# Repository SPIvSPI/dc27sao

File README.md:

# dc27sao

	███████╗██████╗ ██╗██╗   ██╗███████╗██████╗ ██╗
	██╔════╝██╔══██╗██║██║   ██║██╔════╝██╔══██╗██║
	███████╗██████╔╝██║██║   ██║███████╗██████╔╝██║
	╚════██║██╔═══╝ ██║╚██╗ ██╔╝╚════██║██╔═══╝ ██║
	███████║██║     ██║ ╚████╔╝ ███████║██║     ██║
	╚══════╝╚═╝     ╚═╝  ╚═══╝  ╚══════╝╚═╝     ╚═╝

Blackhat spy &amp; Whitehat spy SAO from Def Con 27

The pencil sketch that started it all on June 14th:

Bling bling:

## WTF is all this crap

- `/firmware` - shitty code that runs the blinkenlites
- `/gui` - not-so-shitty gui animation code generator tool (with shittyness added in a rush at the end)
- `/hardware` - schematics and pcb stuff
- `/img` - some pix from the adventure

## Other crap

- The twitters https://twitter.com/SPIvSPI
- Hackaday page https://hackaday.io/project/166811-spivspi-sao-dc27-badge

## Guilty Parties

```
xres0nance - Hardware & firmware
steve/corelit - Over-excellent GUI animation tool
```

## Shoutz n Greetz

```
true, cprossu, aask, & WP crew - 8051 wisdom and moral support
jrwr - crazy drunk russians and a dope-ass hat
MCB - melted lead shoulder-to-shoulder, six pins at a time
woodencyborg - for diving in the deep end with us
pcbway - haulin' ass, gettin' paid
```

and thanks to all our other cheerleaders! couldn't have done it without ya.

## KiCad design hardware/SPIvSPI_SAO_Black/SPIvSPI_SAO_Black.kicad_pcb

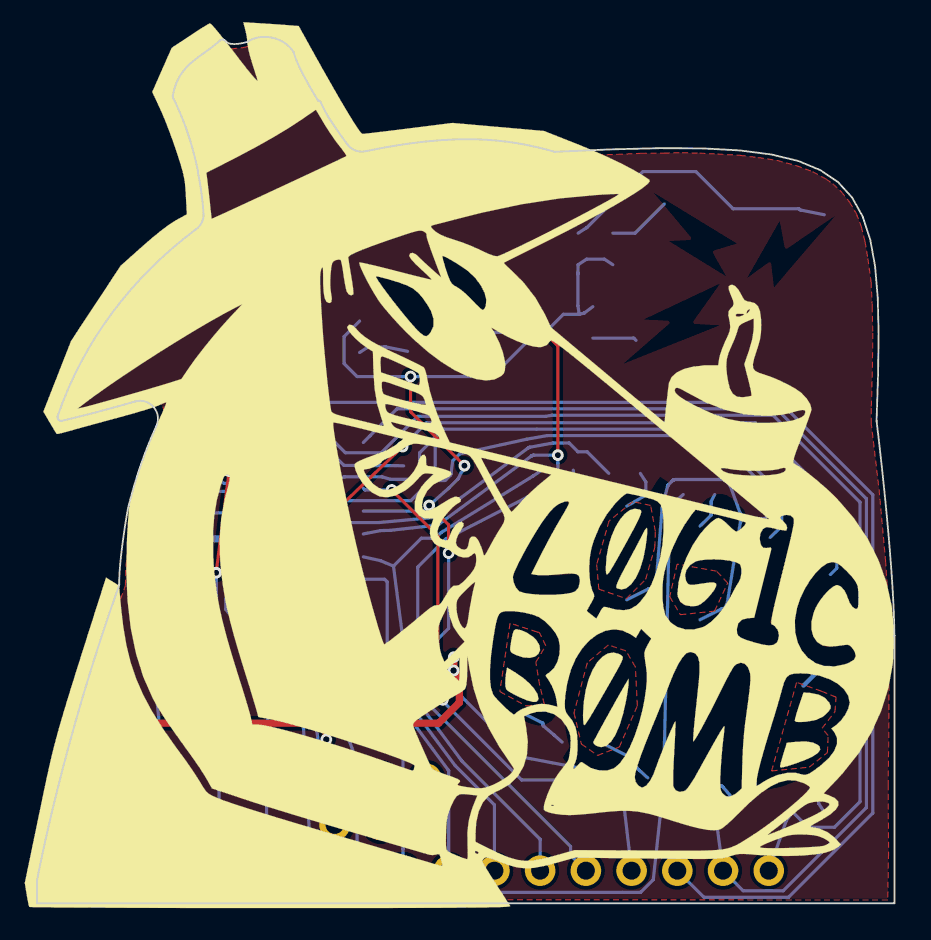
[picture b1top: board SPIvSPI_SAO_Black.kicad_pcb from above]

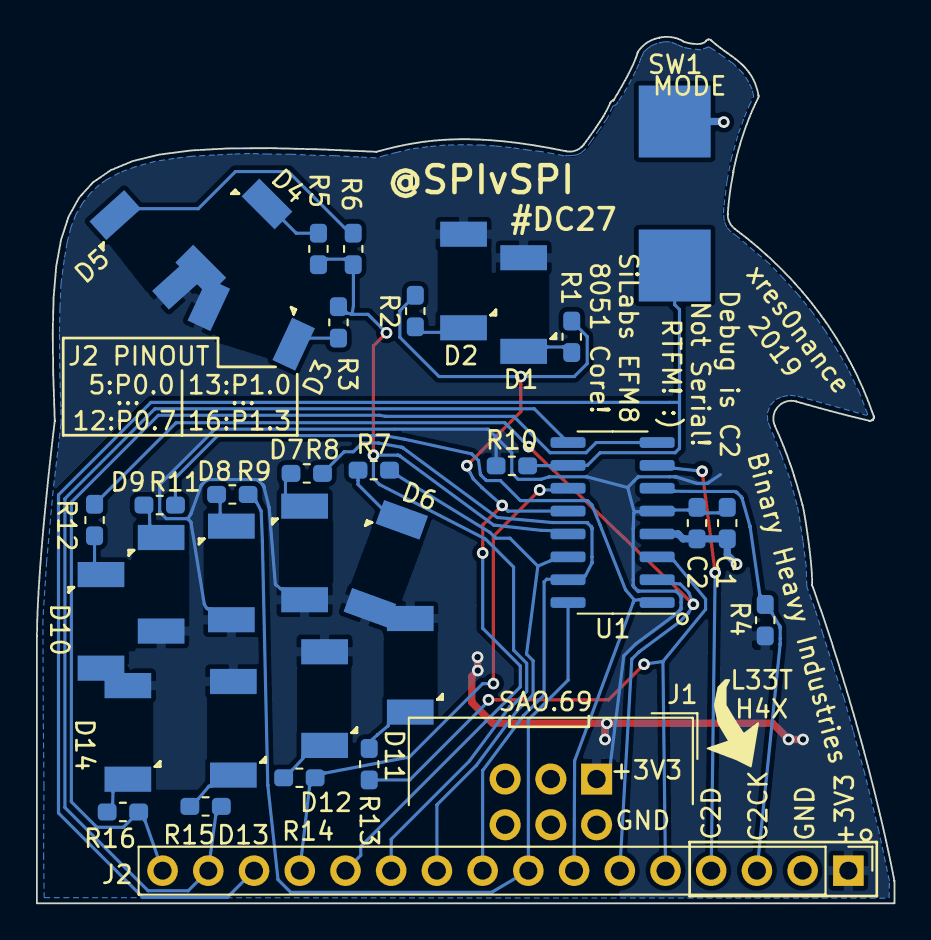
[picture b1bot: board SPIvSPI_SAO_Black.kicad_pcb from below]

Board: 2 copper layers, 47.6 x 48.1 mm, 36 parts (36 on the bottom side), 30 nets.

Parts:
C1: 0.1uF; C_0603_1608Metric_Pad1.05x0.95mm_HandSolder
C2: 10uF; C_0603_1608Metric_Pad1.05x0.95mm_HandSolder
D1, D2: RED; SunLED_3.2x2.8mm_PLCC2_bottom
D3, D4, D5: YEL; SunLED_3.2x2.8mm_PLCC2_bottom
D6, D7, D8, D9, D10, D11, D12, D13, D14: GRN; SunLED_3.2x2.8mm_PLCC2_bottom
J1: SAO.69; IDC-Header_2x03_P2.54mm_Vertical
J2: PROG/BREAKOUT; PinHeader_1x16_P2.54mm_Vertical
R1, R2, R7, R8, R9, R11, R12, R13, R14, R15, R16: 330; R_0603_1608Metric_Pad1.05x0.95mm_HandSolder
R3, R5, R6: 220; R_0603_1608Metric_Pad1.05x0.95mm_HandSolder
R4: 1K; R_0603_1608Metric_Pad1.05x0.95mm_HandSolder
R10: DNP; R_0603_1608Metric_Pad1.05x0.95mm_HandSolder
SW1: MODE; C&K_PTS636_SMD_Tact_6.0x3.5_BACK
U1: EFM8BB10F8G-A-SOIC16; SOIC-16_3.9x9.9mm_P1.27mm

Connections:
+3V3: C1.1, C2.1, D1.2, D2.2, D3.2, D4.2, D5.2, D6.2, D7.2, D8.2, D9.2, D10.2, D11.2, D12.2, D13.2, D14.2, J1.1, J2.1, R4.1, R10.1, U1.5
GND: C1.2, C2.2, J1.2, J2.2, SW1.2, U1.4
unnamed: D1.1, R1.1
unnamed: D2.1, R2.1
unnamed: D3.1, R3.1
unnamed: D4.1, R5.1
unnamed: D5.1, R6.1
unnamed: D6.1, R7.1
unnamed: D7.1, R8.1
unnamed: D8.1, R9.1
unnamed: D9.1, R11.1
unnamed: D10.1, R12.1
unnamed: D11.1, R13.1
unnamed: D12.1, R14.1
unnamed: D13.1, R15.1
unnamed: D14.1, R16.1
unnamed: J2.3, R4.2, U1.6
unnamed: J2.4, U1.7
unnamed: J2.5, R13.2, U1.3
unnamed: J2.6, R12.2, U1.2
unnamed: J2.7, R11.2, U1.1
unnamed: J2.8, R9.2, U1.16
unnamed: J2.9, R8.2, U1.15
unnamed: J2.10, R7.2, U1.14
unnamed: J2.11, R3.2, R5.2, R6.2, U1.13
unnamed: J2.12, R1.2, R2.2, U1.12
unnamed: J2.13, R14.2, U1.11
unnamed: J2.14, R10.2, SW1.1, U1.10
unnamed: J2.15, R15.2, U1.9
unnamed: J2.16, R16.2, U1.8

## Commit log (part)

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2019-07-13 soon
2019-07-13 readme
2019-08-15 stuff
2019-08-15 crap
2020-04-04 Bump acorn from 5.7.3 to 5.7.4 in /gui
    Bumps [acorn](https://github.com/acornjs/acorn) from 5.7.3 to 5.7.4.
    - [Release notes](https://github.com/acornjs/acorn/releases)
    - [Commits](https://github.com/acornjs/acorn/compare/5.7.3...5.7.4)
2020-06-07 Bump websocket-extensions from 0.1.3 to 0.1.4 in /gui
    Bumps [websocket-extensions](https://github.com/faye/websocket-extensions-node) from 0.1.3 to 0.1.4.
    - [Release notes](https://github.com/faye/websocket-extensions-node/releases)
    - [Changelog](https://github.com/faye/websocket-extensions-node/blob/master/CHANGELOG.md)
    - [Commits](https://github.com/faye/websocket-extensions-node/compare/0.1.3...0.1.4)
2020-07-18 Bump lodash from 4.17.15 to 4.17.19 in /gui
    Bumps [lodash](https://github.com/lodash/lodash) from 4.17.15 to 4.17.19.
    - [Release notes](https://github.com/lodash/lodash/releases)
    - [Commits](https://github.com/lodash/lodash/compare/4.17.15...4.17.19)
2020-07-31 Bump elliptic from 6.5.0 to 6.5.3 in /gui
    Bumps [elliptic](https://github.com/indutny/elliptic) from 6.5.0 to 6.5.3.
    - [Release notes](https://github.com/indutny/elliptic/releases)
    - [Commits](https://github.com/indutny/elliptic/compare/v6.5.0...v6.5.3)
2020-09-10 Bump http-proxy from 1.17.0 to 1.18.1 in /gui
    Bumps [http-proxy](https://github.com/http-party/node-http-proxy) from 1.17.0 to 1.18.1.
    - [Release notes](https://github.com/http-party/node-http-proxy/releases)
    - [Changelog](https://github.com/http-party/node-http-proxy/blob/master/CHANGELOG.md)
    - [Commits](https://github.com/http-party/node-http-proxy/compare/1.17.0...1.18.1)
2020-09-12 Bump node-fetch from 2.6.0 to 2.6.1 in /gui
    Bumps [node-fetch](https://github.com/bitinn/node-fetch) from 2.6.0 to 2.6.1.
    - [Release notes](https://github.com/bitinn/node-fetch/releases)
    - [Changelog](https://github.com/node-fetch/node-fetch/blob/master/docs/CHANGELOG.md)
    - [Commits](https://github.com/bitinn/node-fetch/compare/v2.6.0...v2.6.1)
2020-11-25 Bump highlight.js from 9.15.8 to 9.18.5 in /gui
    Bumps [highlight.js](https://github.com/highlightjs/highlight.js) from 9.15.8 to 9.18.5.
    - [Release notes](https://github.com/highlightjs/highlight.js/releases)
    - [Changelog](https://github.com/highlightjs/highlight.js/blob/9.18.5/CHANGES.md)
    - [Commits](https://github.com/highlightjs/highlight.js/compare/9.15.8...9.18.5)
2021-03-09 Bump elliptic from 6.5.0 to 6.5.4 in /gui
    Bumps [elliptic](https://github.com/indutny/elliptic) from 6.5.0 to 6.5.4.
    - [Release notes](https://github.com/indutny/elliptic/releases)
    - [Commits](https://github.com/indutny/elliptic/compare/v6.5.0...v6.5.4)
2021-03-11 Bump dot-prop from 4.2.0 to 4.2.1 in /gui
    Bumps [dot-prop](https://github.com/sindresorhus/dot-prop) from 4.2.0 to 4.2.1.
    - [Release notes](https://github.com/sindresorhus/dot-prop/releases)
    - [Commits](https://github.com/sindresorhus/dot-prop/compare/v4.2.0...v4.2.1)
2021-03-11 Bump yargs-parser from 5.0.0 to 5.0.1 in /gui
    Bumps [yargs-parser](https://github.com/yargs/yargs-parser) from 5.0.0 to 5.0.1.
    - [Release notes](https://github.com/yargs/yargs-parser/releases)
    - [Changelog](https://github.com/yargs/yargs-parser/blob/v5.0.1/CHANGELOG.md)
    - [Commits](https://github.com/yargs/yargs-parser/compare/v5.0.0...v5.0.1)
2021-05-08 Bump url-parse from 1.4.7 to 1.5.1 in /gui
    Bumps [url-parse](https://github.com/unshiftio/url-parse) from 1.4.7 to 1.5.1.
    - [Release notes](https://github.com/unshiftio/url-parse/releases)
    - [Commits](https://github.com/unshiftio/url-parse/compare/1.4.7...1.5.1)
2021-05-10 Bump lodash from 4.17.19 to 4.17.21 in /gui
    Bumps [lodash](https://github.com/lodash/lodash) from 4.17.19 to 4.17.21.
    - [Release notes](https://github.com/lodash/lodash/releases)
    - [Commits](https://github.com/lodash/lodash/compare/4.17.19...4.17.21)
2021-05-11 Bump hosted-git-info from 2.7.1 to 2.8.9 in /gui
    Bumps [hosted-git-info](https://github.com/npm/hosted-git-info) from 2.7.1 to 2.8.9.
    - [Release notes](https://github.com/npm/hosted-git-info/releases)
    - [Changelog](https://github.com/npm/hosted-git-info/blob/v2.8.9/CHANGELOG.md)
    - [Commits](https://github.com/npm/hosted-git-info/compare/v2.7.1...v2.8.9)
2021-05-25 Bump browserslist from 4.6.6 to 4.16.6 in /gui
    Bumps [browserslist](https://github.com/browserslist/browserslist) from 4.6.6 to 4.16.6.
    - [Release notes](https://github.com/browserslist/browserslist/releases)
    - [Changelog](https://github.com/browserslist/browserslist/blob/main/CHANGELOG.md)
    - [Commits](https://github.com/browserslist/browserslist/compare/4.6.6...4.16.6)
2021-05-28 Bump dns-packet from 1.3.1 to 1.3.4 in /gui
    Bumps [dns-packet](https://github.com/mafintosh/dns-packet) from 1.3.1 to 1.3.4.
    - [Release notes](https://github.com/mafintosh/dns-packet/releases)
    - [Changelog](https://github.com/mafintosh/dns-packet/blob/master/CHANGELOG.md)
    - [Commits](https://github.com/mafintosh/dns-packet/compare/v1.3.1...v1.3.4)
2021-06-05 Bump ws from 6.2.1 to 6.2.2 in /gui
    Bumps [ws](https://github.com/websockets/ws) from 6.2.1 to 6.2.2.
    - [Release notes](https://github.com/websockets/ws/releases)
    - [Commits](https://github.com/websockets/ws/commits)
    ---
    updated-dependencies:
    - dependency-name: ws
2021-08-11 Bump path-parse from 1.0.6 to 1.0.7 in /gui
    Bumps [path-parse](https://github.com/jbgutierrez/path-parse) from 1.0.6 to 1.0.7.
    - [Release notes](https://github.com/jbgutierrez/path-parse/releases)
    - [Commits](https://github.com/jbgutierrez/path-parse/commits/v1.0.7)
    ---
    updated-dependencies:
    - dependency-name: path-parse
2021-10-06 Bump url-parse from 1.4.7 to 1.5.3 in /gui
    Bumps [url-parse](https://github.com/unshiftio/url-parse) from 1.4.7 to 1.5.3.
    - [Release notes](https://github.com/unshiftio/url-parse/releases)
    - [Commits](https://github.com/unshiftio/url-parse/compare/1.4.7...1.5.3)
    ---
    updated-dependencies:
    - dependency-name: url-parse
2022-01-13 Bump follow-redirects from 1.7.0 to 1.14.7 in /gui
    Bumps [follow-redirects](https://github.com/follow-redirects/follow-redirects) from 1.7.0 to 1.14.7.
    - [Release notes](https://github.com/follow-redirects/follow-redirects/releases)
    - [Commits](https://github.com/follow-redirects/follow-redirects/compare/v1.7.0...v1.14.7)
    ---
    updated-dependencies:
    - dependency-name: follow-redirects
2022-02-12 Bump ajv from 6.10.2 to 6.12.6 in /gui
    Bumps [ajv](https://github.com/ajv-validator/ajv) from 6.10.2 to 6.12.6.
    - [Release notes](https://github.com/ajv-validator/ajv/releases)
    - [Commits](https://github.com/ajv-validator/ajv/compare/v6.10.2...v6.12.6)
    ---
    updated-dependencies:
    - dependency-name: ajv
2022-02-12 Bump follow-redirects from 1.7.0 to 1.14.8 in /gui
    Bumps [follow-redirects](https://github.com/follow-redirects/follow-redirects) from 1.7.0 to 1.14.8.
    - [Release notes](https://github.com/follow-redirects/follow-redirects/releases)
    - [Commits](https://github.com/follow-redirects/follow-redirects/compare/v1.7.0...v1.14.8)
    ---
    updated-dependencies:
    - dependency-name: follow-redirects
2022-02-18 Bump url-parse from 1.4.7 to 1.5.7 in /gui
    Bumps [url-parse](https://github.com/unshiftio/url-parse) from 1.4.7 to 1.5.7.
    - [Release notes](https://github.com/unshiftio/url-parse/releases)
    - [Commits](https://github.com/unshiftio/url-parse/compare/1.4.7...1.5.7)
    ---
    updated-dependencies:
    - dependency-name: url-parse
2022-02-26 Bump url-parse from 1.4.7 to 1.5.10 in /gui
    Bumps [url-parse](https://github.com/unshiftio/url-parse) from 1.4.7 to 1.5.10.
    - [Release notes](https://github.com/unshiftio/url-parse/releases)
    - [Commits](https://github.com/unshiftio/url-parse/compare/1.4.7...1.5.10)
    ---
    updated-dependencies:
    - dependency-name: url-parse
2022-06-01 Bump eventsource from 1.0.7 to 1.1.1 in /gui
    Bumps [eventsource](https://github.com/EventSource/eventsource) from 1.0.7 to 1.1.1.
    - [Release notes](https://github.com/EventSource/eventsource/releases)
    - [Changelog](https://github.com/EventSource/eventsource/blob/master/HISTORY.md)
    - [Commits](https://github.com/EventSource/eventsource/compare/v1.0.7...v1.1.1)
    ---
    updated-dependencies:
2022-06-25 Bump node-fetch from 2.6.1 to 2.6.7 in /gui
    Bumps [node-fetch](https://github.com/node-fetch/node-fetch) from 2.6.1 to 2.6.7.
    - [Release notes](https://github.com/node-fetch/node-fetch/releases)
    - [Commits](https://github.com/node-fetch/node-fetch/compare/v2.6.1...v2.6.7)
    ---
    updated-dependencies:
    - dependency-name: node-fetch
2022-07-18 Bump thenify from 3.3.0 to 3.3.1 in /gui
    Bumps [thenify](https://github.com/thenables/thenify) from 3.3.0 to 3.3.1.
    - [Release notes](https://github.com/thenables/thenify/releases)
    - [Changelog](https://github.com/thenables/thenify/blob/master/History.md)
    - [Commits](https://github.com/thenables/thenify/compare/3.3.0...3.3.1)
    ---
    updated-dependencies:
2022-07-20 Bump terser from 4.1.2 to 4.8.1 in /gui
    Bumps [terser](https://github.com/terser/terser) from 4.1.2 to 4.8.1.
    - [Release notes](https://github.com/terser/terser/releases)
    - [Changelog](https://github.com/terser/terser/blob/master/CHANGELOG.md)
    - [Commits](https://github.com/terser/terser/commits)
    ---
    updated-dependencies:
2022-11-18 Bump loader-utils and @vue/cli-service in /gui
    Bumps [loader-utils](https://github.com/webpack/loader-utils) to 1.4.2 and updates ancestor dependency [@vue/cli-service](https://github.com/vuejs/vue-cli/tree/HEAD/packages/@vue/cli-service). These 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
    Updates `loader-utils` from 1.2.3 to 1.4.2
    - [Release notes](https://github.com/webpack/loader-utils/releases)
    - [Changelog](https://github.com/webpack/loader-utils/blob/v1.4.2/CHANGELOG.md)
    - [Commits](https://github.com/webpack/loader-utils/compare/v1.2.3...v1.4.2)
    Updates `@vue/cli-service` from 3.9.3 to 5.0.8
2022-12-04 Bump decode-uri-component from 0.2.0 to 0.2.2 in /gui
    Bumps [decode-uri-component](https://github.com/SamVerschueren/decode-uri-component) from 0.2.0 to 0.2.2.
    - [Release notes](https://github.com/SamVerschueren/decode-uri-component/releases)
    - [Commits](https://github.com/SamVerschueren/decode-uri-component/compare/v0.2.0...v0.2.2)
    ---
    updated-dependencies:
    - dependency-name: decode-uri-component
2022-12-09 Bump qs from 6.5.2 to 6.5.3 in /gui
    Bumps [qs](https://github.com/ljharb/qs) from 6.5.2 to 6.5.3.
    - [Release notes](https://github.com/ljharb/qs/releases)
    - [Changelog](https://github.com/ljharb/qs/blob/main/CHANGELOG.md)
    - [Commits](https://github.com/ljharb/qs/compare/v6.5.2...v6.5.3)
    ---
    updated-dependencies:
2022-12-11 Bump express from 4.17.1 to 4.18.2 in /gui
    Bumps [express](https://github.com/expressjs/express) from 4.17.1 to 4.18.2.
    - [Release notes](https://github.com/expressjs/express/releases)
    - [Changelog](https://github.com/expressjs/express/blob/master/History.md)
    - [Commits](https://github.com/expressjs/express/compare/4.17.1...4.18.2)
    ---
    updated-dependencies:
2023-01-01 Bump json5, @vue/cli-service and sass-loader in /gui
    ---
    updated-dependencies:
    - dependency-name: json5
    dependency-type: indirect
    - dependency-name: "@vue/cli-service"
    dependency-type: direct:development
